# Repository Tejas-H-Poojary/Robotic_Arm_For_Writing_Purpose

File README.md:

# 3-DOF Robotic Writing Arm

A 3 degree-of-freedom robotic arm that writes any sentence you type. The project covers the full chain: mechanical design in CAD, a custom KiCad PCB, kinematics in MATLAB, a RoboDK simulation, a machine learning model, and Arduino firmware that drives the real arm.

> **Author:** Tejas
> **Tools:** Fusion 360 · KiCad · MATLAB (Robotics Toolbox) · RoboDK · Python · Arduino IDE · Tinkercad

▶ *Click the image above to watch the simulation video.*

---

## Table of Contents

1. [Overview](#1-overview)
2. [System Architecture](#2-system-architecture)
3. [Repository Structure](#3-repository-structure)
4. [Hardware and Bill of Materials](#4-hardware-and-bill-of-materials)
5. [CAD Design](#5-cad-design)
6. [Electronics and KiCad PCB](#6-electronics-and-kicad-pcb)
7. [Kinematics in MATLAB](#7-kinematics-in-matlab)
8. [Simulation in RoboDK](#8-simulation-in-robodk)
9. [Machine Learning Model](#9-machine-learning-model)
10. [Text to Motion (Python)](#10-text-to-motion-python)
11. [Arduino Firmware](#11-arduino-firmware)
12. [How to Run](#12-how-to-run)

---

## 1. Overview

**Goal:** give the arm a sentence and have it write that sentence on paper.

**What was built:**

- A 3-DOF arm designed in CAD, with a servo-driven joint set and a stepper-driven pen mechanism.
- A custom PCB (KiCad) with power regulation, motor drivers and sensor inputs.
- A kinematic model in MATLAB: DH parameters, forward kinematics, Jacobian, velocity and singularity analysis.
- A simulation in RoboDK to test motions before running the real arm.
- A machine learning model that learns the mapping between end-effector position and joint angles from a dataset generated by the kinematic model.
- Arduino firmware that receives joint angles over serial and drives the servos and stepper, with a force-feedback PID for pen pressure.

---

## 2. System Architecture

```
Sentence ──► Single-stroke font ──► (x, y, pen) points
                                         │
                                         ▼
                            ML model / inverse kinematics
                                         │
                                         ▼
                              Joint angles (q1 ... qn)
                                         │
                                  USB serial (Python)
                                         ▼
                      Arduino Nano ──► Servos + Stepper (pen lift)
                            ▲
                            └── Force sensor (pen pressure PID)
```

---

## 3. Repository Structure

```
robotic-arm-5dof/
├── Arduino_code/         # Arduino firmware (.ino)
├── cad/                  # Fusion 360 files and STL exports
├── docs/
│   ├── images/           # Screenshots used in this README
│   └── videos/           # Simulation video
├── mathlab/              # DH model, kinematics, Jacobian, singularity scripts
├── ml/                   # Dataset generation, training and evaluation
├── pcb/                  # KiCad project (schematic, PCB layout, Gerbers)
├── python/               # Text-to-motion script and serial sender
├── tinkercad/            # Tinkercad Circuits files
└── README.md
```

---

## 4. Hardware and Bill of Materials

| Part | Qty | Notes |
|---|---|---|
| Arduino Nano | 1 | Main controller |
| Servo motors | TBD | Joint actuators (model: TBD) |
| 28BYJ-48 stepper motor | 1 | Pen lift mechanism |
| ULN2003 driver | 1 | Stepper driver |
| LM2596S-ADJ buck converter | 2 | One for Nano logic rail, one for servo/stepper rail |
| Force sensor (FSR) | 1 | Pen pressure feedback on A0 |
| Schottky diode, inductors, capacitors, resistors |
| Power supply | 1 | 10 V to 30 V input |
| Screw terminals | TBD | Motor, sensor and supply connections |

---

## 5. CAD Design

The arm was modelled in **Fusion 360**.

**Design steps:**

1. Defined the workspace and the reach needed to cover a sheet of paper.
2. Modelled each link and joint bracket with the servo mounting dimensions.
3. Designed the pen holder with a stepper-driven lift mechanism.
4. Assembled all parts with joints and checked the range of motion.
5. Exported parts as STL for 3D printing, and as a STEP file for RoboDK.

---

## 6. Electronics and KiCad PCB

### 6.1 Circuit description

- **Power input:** 10 V to 30 V supply through a Schottky protection diode and a 470 uF input capacitor.
- **Buck converters:** two LM2596S-ADJ regulators set to about 5 V with a 3k / 1k feedback divider.
  - One feeds the Arduino Nano's 5 V pin.
  - One feeds the servos and the stepper driver.
- **Servo connectors:** 3-pin terminals (power, signal, ground) with a bulk capacitor on the servo rail.
- **Stepper driver:** ULN2003 driving the 28BYJ-48, with the motor common wired to the servo/stepper rail.
- **Force sensor:** FSR from 5 V to A0 with a 10k pull-down resistor to ground.

| Signal | Arduino Nano pin |
|---|---|
| Servo 1 signal | D3 |
| Servo 2 signal | D5 |
| Stepper IN1 to IN4 | D6 to D9 |
| Force sensor | A0 |

### 6.2 PCB layout

**Design notes:**

- Keep the buck converter switching loop (input capacitor, IC, inductor, diode) short and use wide traces.
- Use a common ground for the Nano, the servo rail and the ULN2003.
- Place 100 nF decoupling capacitors close to the Nano.

---

## 7. Kinematics in MATLAB

All calculations are done in MATLAB with the Robotics Toolbox (Peter Corke).

### 7.1 DH parameters

| Joint | theta (deg) | d | a | alpha (deg) |
|---|---|---|---|---|
| 1 | theta1 | 30 | 0  | 90 |
| 2 | theta2 | 0  | 30 | 0  |
| 3 | theta3 | 0  | 10 | 0  |

### 7.2 Transformation matrix

Each joint uses the standard DH transformation:

```
        | cos(t)  -sin(t)*cos(a)   sin(t)*sin(a)   r*cos(t) |
A(i) =  | sin(t)   cos(t)*cos(a)  -cos(t)*sin(a)   r*sin(t) |
        |   0         sin(a)           cos(a)          d     |
        |   0           0                0             1     |
```

where `t` = theta, `a` = alpha, `r` = link length "a", `d` = link offset.

### 7.3 Arm pose plot

```matlab
KR.plot(q);
KR.teach(q);
```

### 7.4 Jacobian and velocity

```matlab
J  = jacob0(KR, q);          % 6 x N
qd = [qd1, qd2, qd3]';       % joint velocities (rad/s)
V  = J * qd;                 % [vx vy vz wx wy wz]'
```

### 7.5 Singularity analysis

For a non-square Jacobian, the determinant is not defined, so these measures are used instead:

```matlab
w_pos = sqrt(det(J(1:3,:) * J(1:3,:)'));   % position manipulability
r     = rank(J);                           % less than N means singular
s     = svd(J);                            % smallest value near 0 means near-singular
```

The singular joint angles are found symbolically: build `J` with symbolic angles, take `det`, then `factor` it. Each `sin(...)` or `cos(...)` factor that can become zero marks a singular configuration.

---

## 8. Simulation in RoboDK

The arm was simulated in **RoboDK** to check reachability, joint limits and collisions before running the real hardware.

**Steps:**

1. Imported the CAD model (STEP/STL) of each link into RoboDK.
2. Created a robot with 5 joints using the same DH parameters as in MATLAB.
3. Set joint limits and the tool frame (pen tip).
4. Created a reference frame for the paper and added a target for each letter stroke.
5. Ran the motion program and checked for singularities and out-of-reach points.

▶ [Watch the simulation video](robotic-arm-5dof/docs/videos/stimulation_video.gif)

---

## 9. Machine Learning Model

### 9.1 Dataset

The dataset is generated from the MATLAB kinematic model. For each combination of joint angles, the end-effector pose is computed and saved to `dataset.txt`.

### 9.2 SVM model

The dataset contains floating-point (continuous) values, so a **Support Vector Regressor (SVR)** was used. For each input feature, the relationship with the output labels was plotted to understand how the labels are formed.

---

## 10. Text to Motion (Python)

The Python script runs on the laptop (VS Code). It converts a typed sentence into pen strokes and joint angles.

**Steps:**

1. Read the sentence from the terminal and wrap it into lines that fit the paper.
2. Convert each letter into single-stroke line segments using the Hershey font.
3. Scale the strokes to the paper size and cut them into small steps (0.2 cm).
4. Convert each `(x, y)` point to joint angles with the ML model or inverse kinematics.
5. Send `q1,q2,pen` lines to the Arduino over USB serial and wait for `ok`.

**Serial protocol**

```
q1,q2,pen\n        example:  41.3,62.0,1
pen = 0  -> pen up
pen = 1  -> pen down
```

---

## 11. Arduino Firmware

The Arduino Nano receives angles from Python and drives the actuators.

**Features:**

- Smooth servo motion with a limited step per loop.
- Stepper-driven pen lift, with a travel limit as a safety.
- **PID on pen pressure:** the force sensor on A0 is read, and the stepper adjusts the pen height to hold a constant force.
- A calibration command (`F`) that prints the current force reading to the Serial Monitor.

**Tunable settings**

| Setting | Meaning |
|---|---|
| `FORCE_CONTACT` | Reading that means the pen touched the paper |
| `FORCE_TARGET` | Pressure to hold while writing |
| `Kp`, `Ki`, `Kd` | PID gains |
| `MAX_PEN_STEPS` | Safety limit for pen travel |
| `PEN_DIR` | Direction of pen movement (1 or -1) |

---

## 12. How to Run

### 12.1 Requirements

- Arduino IDE (libraries: `Servo`, `Stepper`)
- Python 3.10 or newer
- MATLAB with the Robotics Toolbox (for the kinematics)
- RoboDK (for the simulation)

```bash
pip install Hershey-Fonts pyserial numpy scikit-learn
```

### 12.2 Steps

1. **Build the hardware** and wire the board as in the schematic. Power the servos and stepper from the buck rail, never from the Nano's USB power.
2. **Upload the firmware:** open `Arduino_code/` in Arduino IDE, select the Arduino Nano and the port, then click Upload.
3. **Close the Arduino Serial Monitor**, because only one program can use the COM port.
4. **Find the COM port:**

   ```python
   import serial.tools.list_ports
   for p in serial.tools.list_ports.comports():
       print(p.device, "-", p.description)
   ```

5. **Set the port** in the Python script (for example `COM5`).
6. **Run the script:**

   ```bash
   python python/write.py
   ```

7. Type a sentence at the prompt. The arm starts writing.

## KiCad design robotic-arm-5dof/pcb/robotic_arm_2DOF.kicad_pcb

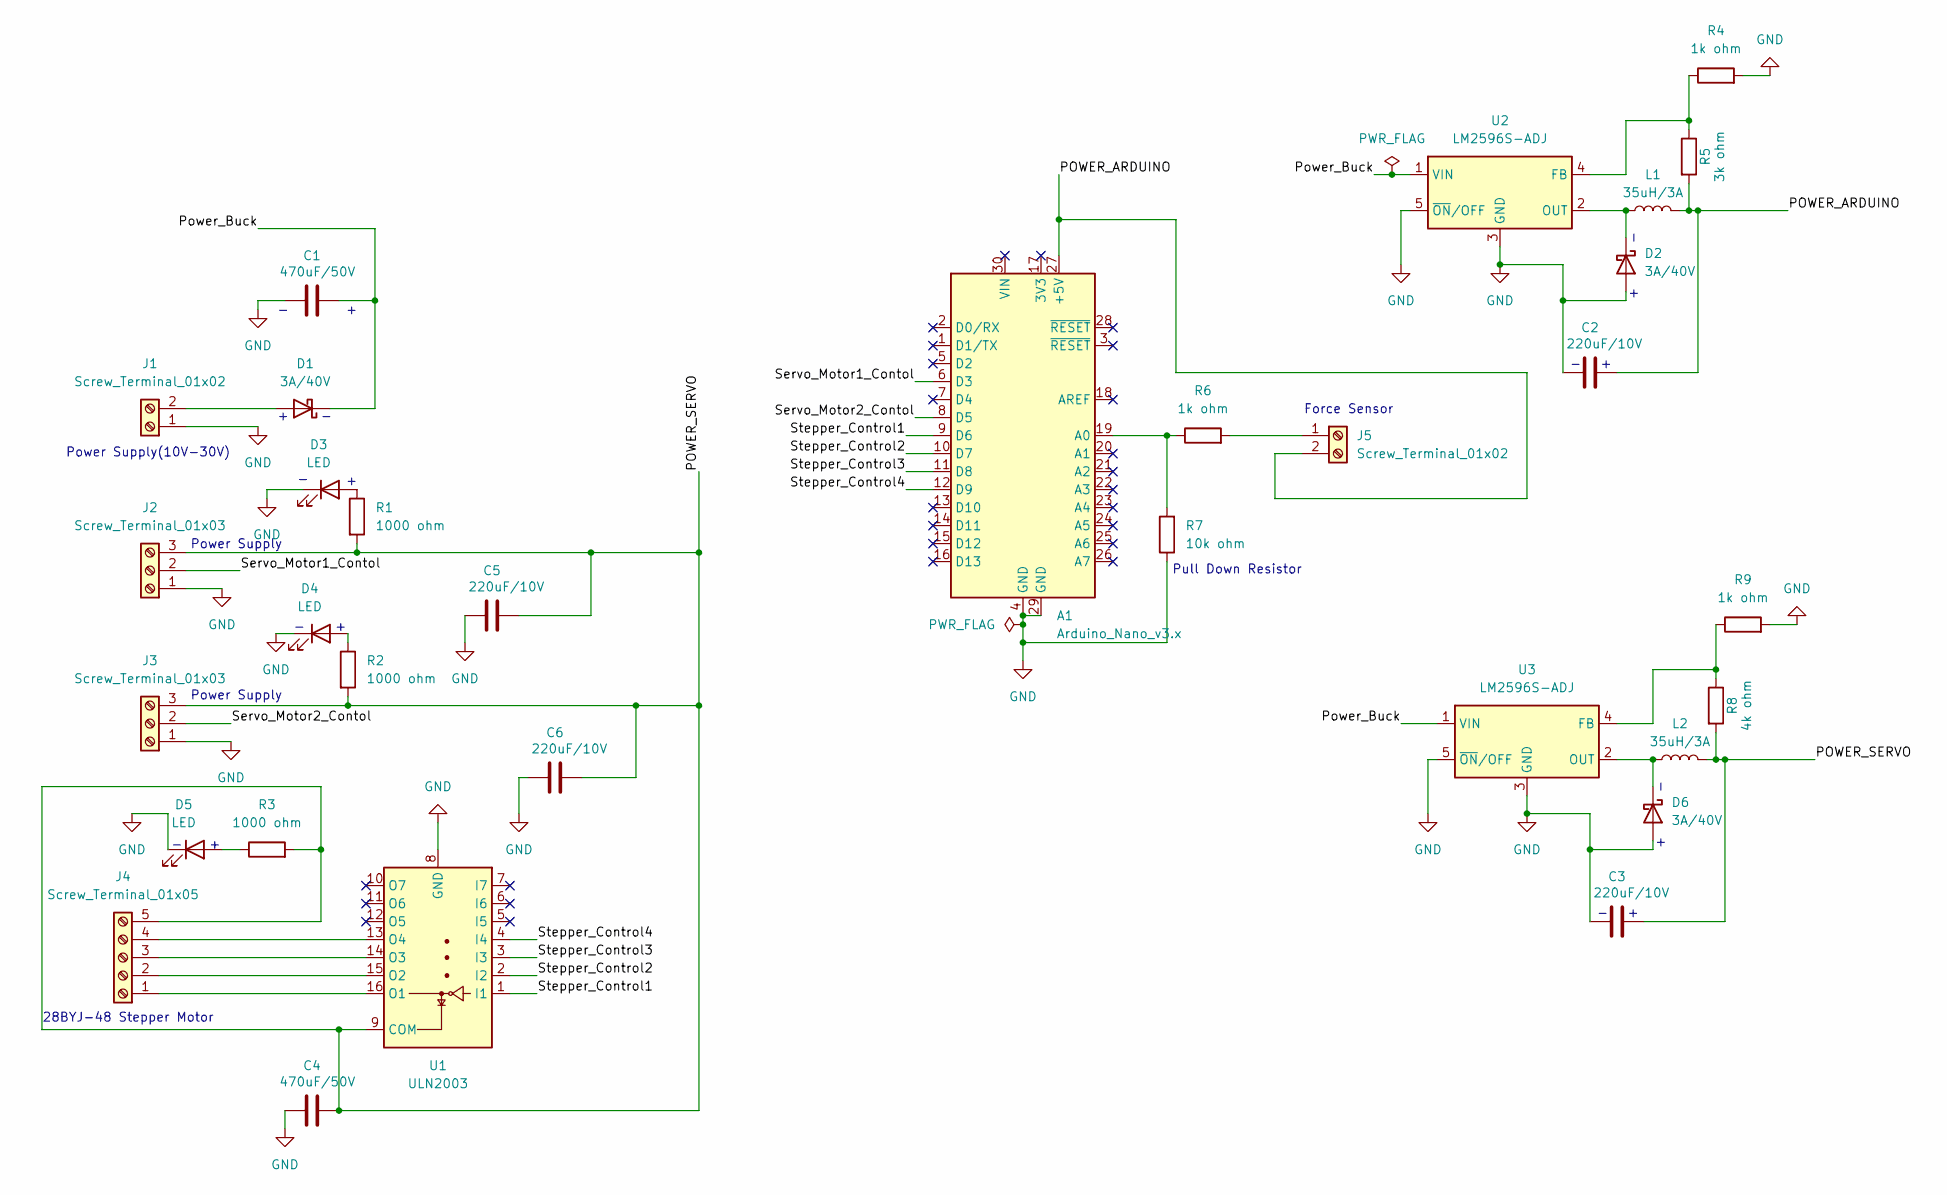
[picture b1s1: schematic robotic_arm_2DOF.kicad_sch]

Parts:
A1: Arduino_Nano_v3.x; Arduino_Nano
C1, C4: 470uF/50V; CP_Radial_D10.0mm_P5.00mm
C2, C3, C5, C6: 220uF/10V; CP_Radial_D6.3mm_P2.50mm
D1, D2, D6: 3A/40V; D_DO-201AD_P15.24mm_Horizontal
D3, D4, D5: LED; LED_D5.0mm
J1, J5: Screw_Terminal_01x02; TerminalBlock_MaiXu_MX126-5.0-02P_1x02_P5.00mm
J2, J3: Screw_Terminal_01x03; TerminalBlock_MaiXu_MX126-5.0-03P_1x03_P5.00mm
J4: Screw_Terminal_01x05; TerminalBlock_MaiXu_MX126-5.0-05P_1x05_P5.00mm
L1, L2: 35uH/3A; L_Axial_L16.0mm_D7.5mm_P20.32mm_Horizontal_Fastron_XHBCC
R1, R2, R3: 1000 ohm; R_Axial_DIN0207_L6.3mm_D2.5mm_P10.16mm_Horizontal
R4, R6, R9: 1k ohm; R_Axial_DIN0207_L6.3mm_D2.5mm_P10.16mm_Horizontal
R5: 3k ohm; R_Axial_DIN0207_L6.3mm_D2.5mm_P10.16mm_Horizontal
R7: 10k ohm; R_Axial_DIN0207_L6.3mm_D2.5mm_P10.16mm_Horizontal
R8: 4k ohm; R_Axial_DIN0207_L6.3mm_D2.5mm_P10.16mm_Horizontal
U1: ULN2003; DIP-16_W7.62mm_Socket
U2, U3: LM2596S-ADJ; TO-263-5_TabPin3

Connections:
/POWER_ARDUINO: A1.27 (+5V), C2.2, J5.2, L1.2, R5.2
/POWER_SERVO: C3.2, C4.2, C5.2, C6.2, J2.3, J3.3, J4.5, L2.2, R1.2, R2.2, R3.2, R8.2, U1.9 (COM)
/Power_Buck: C1.2, D1.1 (K), U2.1 (VIN), U3.1 (VIN)
/Servo_Motor1_Contol: A1.6 (D3), J2.2
/Servo_Motor2_Contol: A1.8 (D5), J3.2
/Stepper_Control1: A1.9 (D6), U1.1 (I1)
/Stepper_Control2: A1.10 (D7), U1.2 (I2)
/Stepper_Control3: A1.11 (D8), U1.3 (I3)
/Stepper_Control4: A1.12 (D9), U1.4 (I4)
GND: A1.4 (GND), A1.29 (GND), C1.1, C2.1, C3.1, C4.1, C5.1, C6.1, D2.2 (A), D3.1 (K), D4.1 (K), D5.1 (K), D6.2 (A), J1.1, J2.1, J3.1, R4.2, R7.1, R9.2, U1.8 (GND), U2.3 (GND), U2.5 (~ON/OFF), U3.3 (GND), U3.5 (~ON/OFF)
unnamed: A1.19 (A0), R6.1, R7.2
unnamed: D1.2 (A), J1.2
unnamed: D2.1 (K), L1.1, U2.2 (OUT)
unnamed: D3.2 (A), R1.1
unnamed: D4.2 (A), R2.1
unnamed: D5.2 (A), R3.1
unnamed: D6.1 (K), L2.1, U3.2 (OUT)
unnamed: J4.1, U1.16 (O1)
unnamed: J4.2, U1.15 (O2)
unnamed: J4.3, U1.14 (O3)
unnamed: J4.4, U1.13 (O4)
unnamed: J5.1, R6.2
unnamed: R4.1, R5.1, U2.4 (FB)
unnamed: R8.1, R9.1, U3.4 (FB)

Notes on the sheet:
Force Sensor
Pull Down Resistor
28BYJ-48 Stepper Motor
Power Supply(10V-30V)
Power Supply

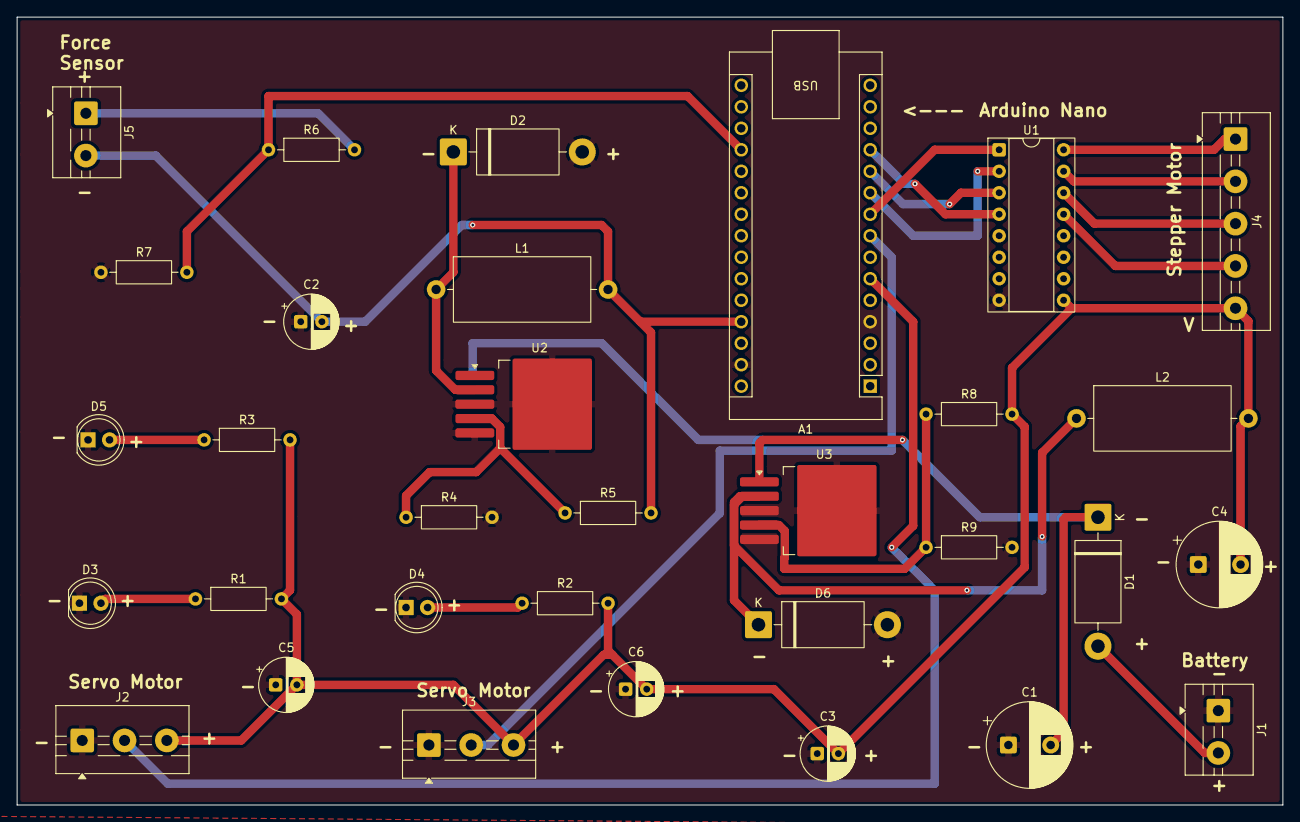
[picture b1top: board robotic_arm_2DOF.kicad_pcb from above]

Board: 2 copper layers, 149.6 x 93.1 mm, 32 parts (0 on the bottom side), 24 nets.
